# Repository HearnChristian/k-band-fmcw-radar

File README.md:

# K-Band FMCW Radar

A frequency-modulated continuous-wave (FMCW) radar front-end designed in KiCad —
a single-board transceiver intended for **ground-based ranging and weather /
precipitation sensing**. This repository holds the schematic capture, the
project's custom KiCad libraries, and the generated netlist. Work in progress.

## Architecture

FMCW radar works by transmitting a continuous tone whose frequency is swept
(chirped) linearly in time, then mixing the received echo against the
transmitted signal. The frequency of the resulting beat tone is proportional to
target range, so the whole signal chain is built around generating a clean,
linear chirp and digitizing the low-frequency beat note.

```
  Reference        Chirp synth        RF transceiver        Driver amp
  ┌────────┐      ┌──────────┐       ┌──────────────┐      ┌──────────┐
  │  TCXO  │─────▶│ ADF4159  │──────▶│ BGT24LTR11N16│─────▶│AMM-8211PSM│──▶ TX
  │ ref clk│      │ PLL/ramp │       │ 24 GHz Tx/Rx │      │ driver PA │
  └────────┘      └──────────┘       └──────┬───────┘      └──────────┘
                                            │ IF (beat)
                                            ▼
                       ┌──────────┐   ┌──────────┐   ┌──────────┐
                  Rx ──│ OPA1656  │──▶│ ADS8353  │──▶│ FT2232H  │──▶ USB host
                       │ IF amp   │   │ 16b ADC  │   │ USB 2.0  │
                       └──────────┘   └──────────┘   └──────────┘
```

## Key components

| Block | Part | Function |
|-------|------|----------|
| Chirp synthesizer | **ADF4159** | Fractional-N PLL with onboard ramp generator — produces the linear FMCW sweep |
| RF transceiver | **BGT24LTR11N16** | 24 GHz SiGe transmit/receive front-end with integrated VCO and downconversion |
| Driver amplifier | **AMM-8211PSM** | 22–57 GHz GaAs MMIC driver amp boosting the transmit chain |
| IF / baseband | **OPA1656** | Low-noise, low-distortion op-amp conditioning the beat-note signal |
| Data converter | **ADS8353** | Dual 16-bit SAR ADC sampling the IF |
| Host interface | **FT2232HL** | USB 2.0 bridge for control + data streaming |
| Reference clock | **ECS-TXO-2520MV** | TCXO frequency reference |
| Power | **TPS7A4700 / TPS7A2018 / TPS7A2033** | Ultra-low-noise LDOs for clean RF/analog rails |
| Config | **93LC56B** | EEPROM for FT2232 descriptor |

## Custom library work

The **AMM-8211PSM** driver amplifier had no vendor-supplied EDA data — only a
datasheet — so its schematic symbol and PCB footprint were built from scratch
from the Marki Microwave mechanical drawings:

```
AMM-8211PSM.kicad_sym                                          custom symbol
AMM-8211PSM.pretty/QFN-16-1EP_3x3mm_P0.5mm_EP1.1x1.1mm_Marki.kicad_mod   custom footprint
```

The footprint is a 3 × 3 mm 16-lead QFN, 0.5 mm pitch, with a 1.10 × 1.10 mm
exposed ground paddle and a 3 × 3 array of thermal vias, matching the Marki
outline drawing and pin assignment.

## Repository layout

```
Radar1.kicad_pro      KiCad project
Radar1.kicad_sch      Schematic (in progress)
Radar1.kicad_pcb      PCB layout (not yet started)
Radar1.net            Exported netlist
AMM-8211PSM.kicad_sym Custom symbol (see above)
AMM-8211PSM.pretty/   Custom footprint library
sym-lib-table         Project symbol-library table
fp-lib-table          Project footprint-library table
```

## Tools

Designed in [KiCad](https://www.kicad.org/) 9. Open `Radar1.kicad_pro` to view
the schematic.

---

*Author: Christian Hearn*

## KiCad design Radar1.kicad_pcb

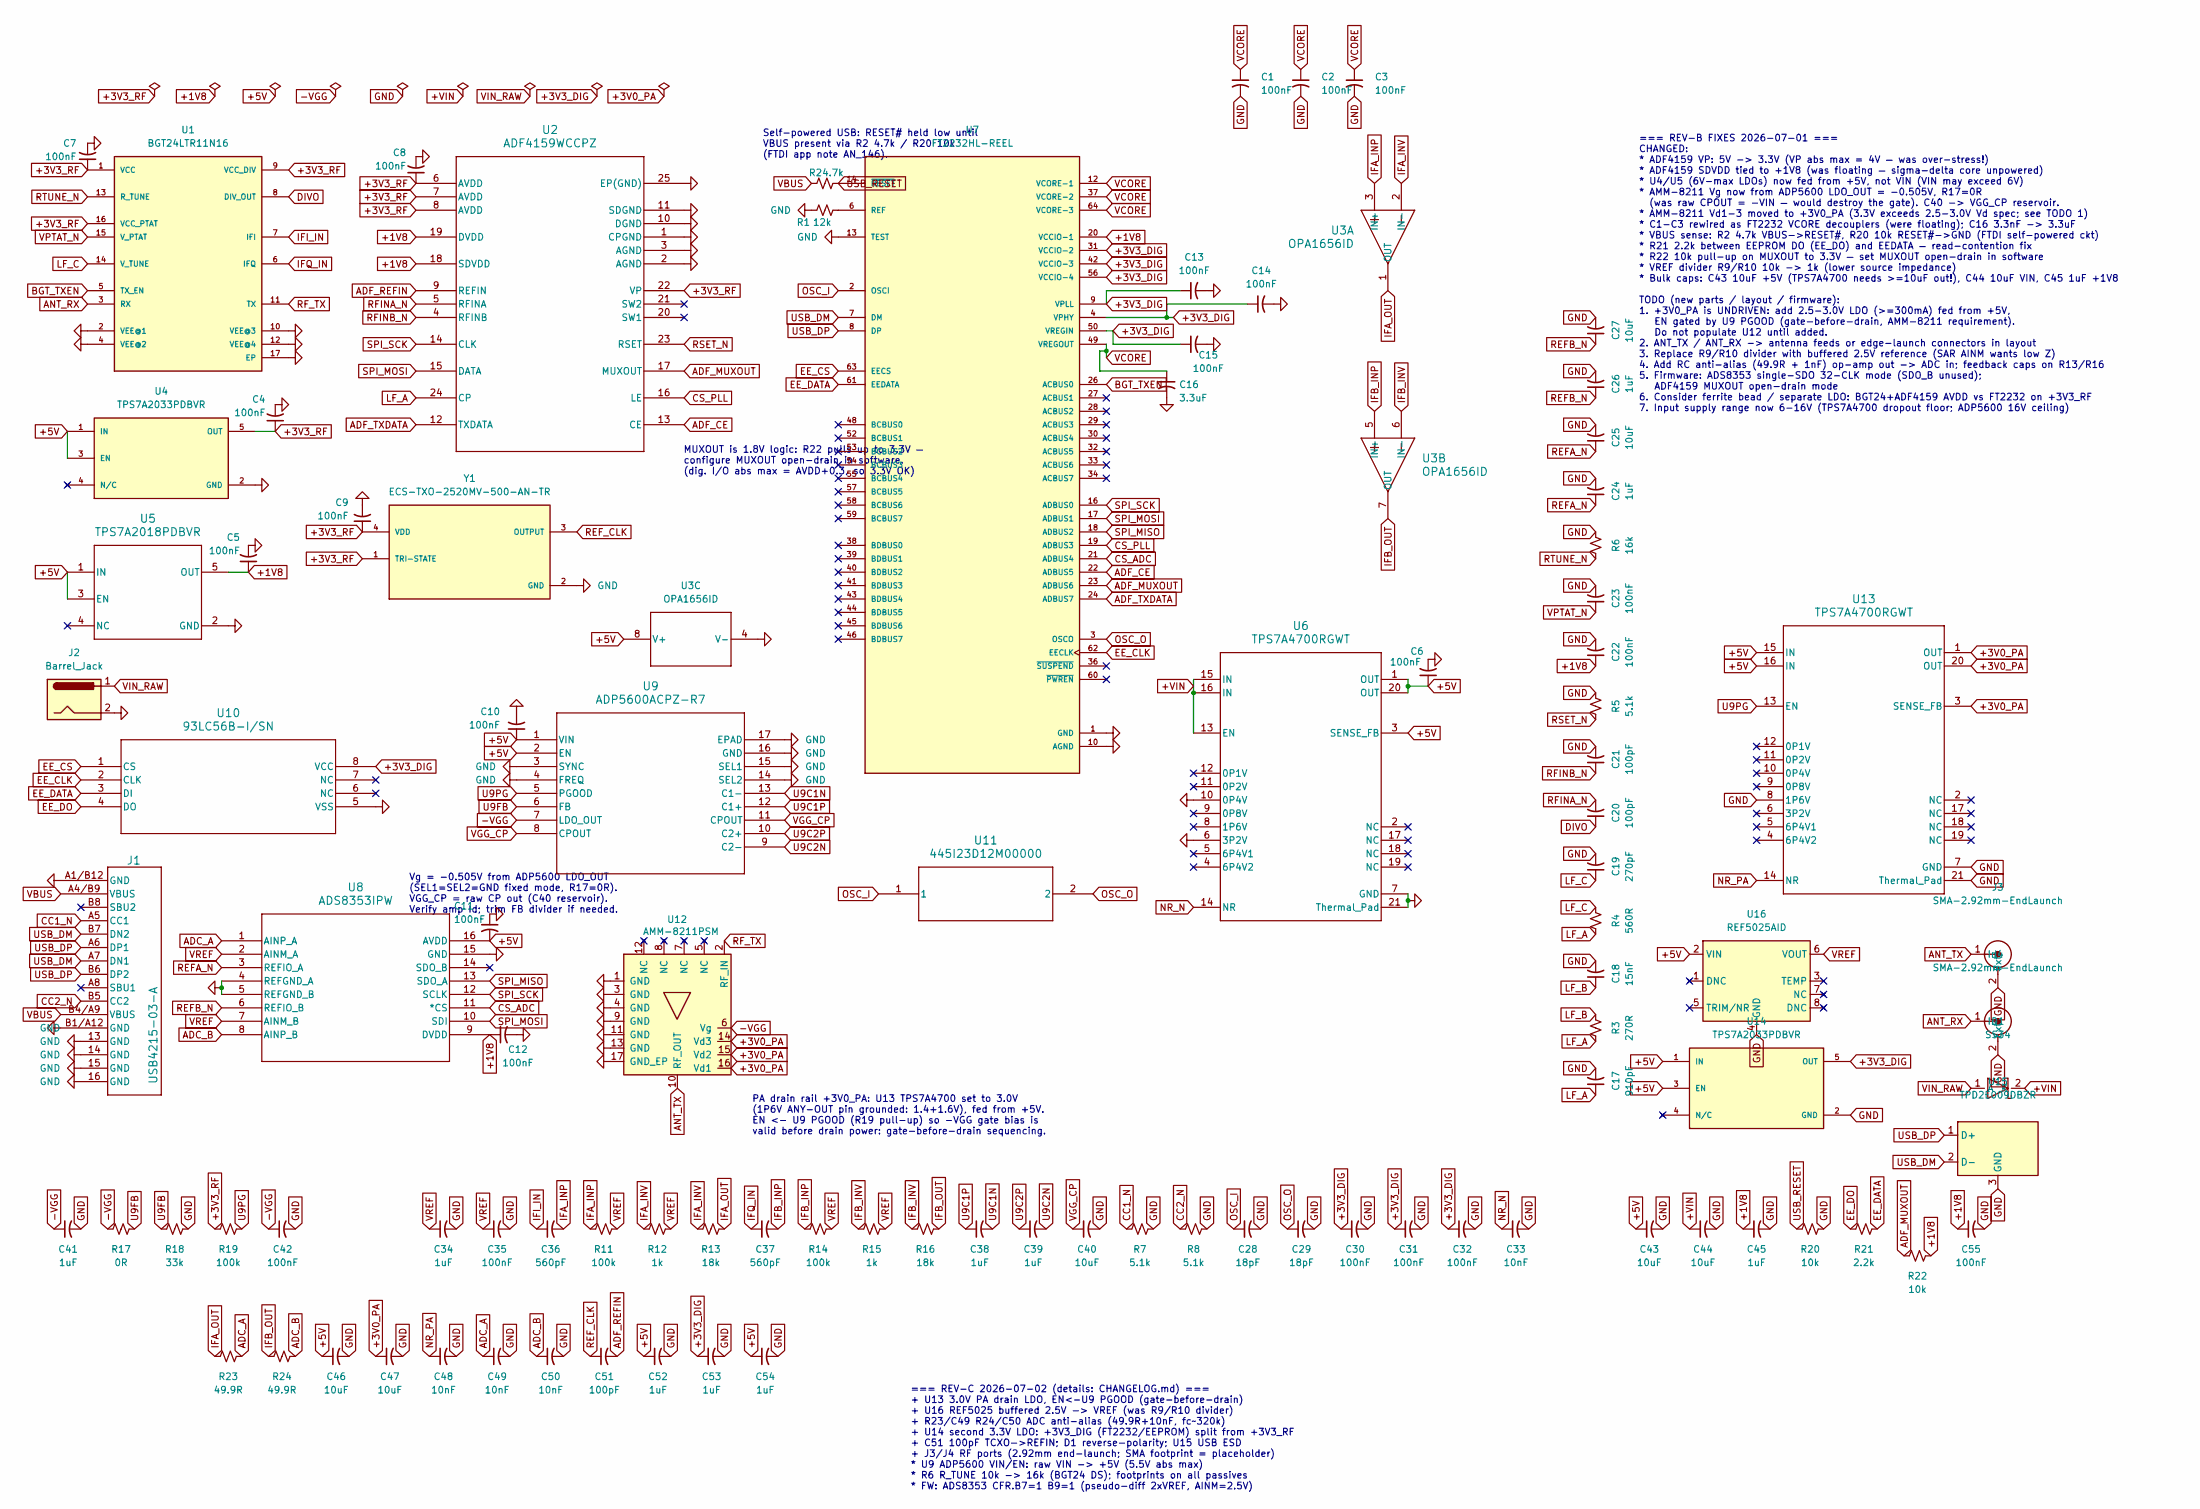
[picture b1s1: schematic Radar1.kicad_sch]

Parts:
C1, C2, C3, C4, C5, C6, C7, C8, C9, C10, C11, C12, C13, C14, C15, C22, C23, C30, C31, C32, C35, C42, C55: 100nF; C_0603_1608Metric
C16: 3.3uF; C_0805_2012Metric
C17: 910pF; C_0603_1608Metric
C18: 15nF; C_0603_1608Metric
C19: 270pF; C_0603_1608Metric
C20, C21, C51: 100pF; C_0603_1608Metric
C24, C26, C34, C38, C39, C41, C45, C52, C53, C54: 1uF; C_0603_1608Metric
C25, C27, C40, C43, C44, C46, C47: 10uF; C_0805_2012Metric
C28, C29: 18pF; C_0603_1608Metric
C33, C48, C49, C50: 10nF; C_0603_1608Metric
C36, C37: 560pF; C_0603_1608Metric
D1: SS34; D_SMA
J1: USB4215-03-A; CONN_8p94X6p5X3p16_12L_GCC
J2: Barrel_Jack; BarrelJack_Horizontal
J3, J4: SMA-2.92mm-EndLaunch; SMA_Amphenol_132289_EdgeMount
R1: 12k; R_0603_1608Metric
R2: 4.7k; R_0603_1608Metric
R3: 270R; R_0603_1608Metric
R4: 560R; R_0603_1608Metric
R5, R7, R8: 5.1k; R_0603_1608Metric
R6: 16k; R_0603_1608Metric
R11, R14, R19: 100k; R_0603_1608Metric
R12, R15: 1k; R_0603_1608Metric
R13, R16: 18k; R_0603_1608Metric
R17: 0R; R_0603_1608Metric
R18: 33k; R_0603_1608Metric
R20, R22: 10k; R_0603_1608Metric
R21: 2.2k; R_0603_1608Metric
R23, R24: 49.9R; R_0603_1608Metric
U1: BGT24LTR11N16; PQFN50P240X240X77-17N-V
U2: ADF4159WCCPZ; CP_24_10
U3: OPA1656ID; D0008A_N
U4, U14: TPS7A2033PDBVR; DBV0005A-IPC_A; PARTREV H
U5: TPS7A2018PDBVR; DBV0005A-IPC_A
U6, U13: TPS7A4700RGWT; RGW0020A-IPC_A
U7: FT2232HL-REEL; QFP50P1200X1200X160-64N
U8: ADS8353IPW; PW16_TEX
U9: ADP5600ACPZ-R7; CP-16-17_ADI
U10: 93LC56B-I/SN; SOIC8-N_MC_MCH
U11: 445I23D12M00000; 445I23D12M00000_CTS
U12: AMM-8211PSM; QFN-16-1EP_3x3mm_P0.5mm_EP1.1x1.1mm_Marki; MPN AMM-8211PSM-22
U15: TPD2E009DBZR; SOT-23
U16: REF5025AID; SOIC-8_3.9x4.9mm_P1.27mm
Y1: ECS-TXO-2520MV-500-AN-TR; OSC_ECS-TXO-2520MV-500-AN-TR; PARTREV 2017

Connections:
+1V8: C5.1, C12.1, C22.1, C45.1, C55.1, R22.2, U2.18 (SDVDD), U2.19 (DVDD), U5.5 (OUT), U7.20 (VCCIO-1), U8.9 (DVDD)
+3V0_PA: C47.1, U12.14 (Vd3), U12.15 (Vd2), U12.16 (Vd1), U13.1 (OUT), U13.3 (SENSE_FB), U13.20 (OUT)
+3V3_DIG: C13.1, C14.1, C15.1, C30.1, C31.1, C32.1, C53.1, U7.4 (VPHY), U7.9 (VPLL), U7.31 (VCCIO-2), U7.42 (VCCIO-3), U7.50 (VREGIN), U7.56 (VCCIO-4), U10.8 (VCC), U14.5 (OUT)
+3V3_RF: C4.1, C7.1, C8.1, C9.1, R19.1, U1.1 (VCC), U1.9 (VCC_DIV), U1.16 (VCC_PTAT), U2.6 (AVDD), U2.7 (AVDD), U2.8 (AVDD), U2.22 (VP), U4.5 (OUT), Y1.1 (TRI-STATE), Y1.4 (VDD)
+5V: C6.1, C10.1, C11.2, C43.1, C46.1, C52.1, C54.1, U3.8 (V+), U4.1 (IN), U4.3 (EN), U5.1 (IN), U5.3 (EN), U6.1 (OUT), U6.3 (SENSE_FB), U6.20 (OUT), U8.16 (AVDD), U9.1 (VIN), U9.2 (EN), U13.15 (IN), U13.16 (IN), U14.1 (IN), U14.3 (EN), U16.2 (VIN)
+VIN: C44.1, D1.2 (K), U6.13 (EN), U6.15 (IN), U6.16 (IN)
-VGG: C41.1, C42.1, R17.1, U9.7 (LDO_OUT), U12.6 (Vg)
ADC_A: C49.1, R23.2, U8.1 (AINP_A)
ADC_B: C50.1, R24.2, U8.8 (AINP_B)
ADF_CE: U2.13 (CE), U7.22 (ADBUS5)
ADF_MUXOUT: R22.1, U2.17 (MUXOUT), U7.23 (ADBUS6)
ADF_REFIN: C51.2, U2.9 (REFIN)
ADF_TXDATA: U2.12 (TXDATA), U7.24 (ADBUS7)
ANT_RX: J4.1 (In), U1.3 (RX)
ANT_TX: J3.1 (In), U12.10 (RF_OUT)
BGT_TXEN: U1.5 (TX_EN), U7.26 (ACBUS0)
CC1_N: J1.A5 (CC1), R7.1
CC2_N: J1.B5 (CC2), R8.1
CS_ADC: U7.21 (ADBUS4), U8.11 (*CS)
CS_PLL: U2.16 (LE), U7.19 (ADBUS3)
DIVO: C20.1, U1.8 (DIV_OUT)
EE_CLK: U7.62 (EECLK), U10.2 (CLK)
EE_CS: U7.63 (EECS), U10.1 (CS)
EE_DATA: R21.2, U7.61 (EEDATA), U10.3 (DI)
EE_DO: R21.1, U10.4 (DO)
GND: C1.2, C2.2, C3.2, C4.2, C5.2, C6.2, C7.2, C8.2, C9.2, C10.2, C11.1, C12.2, C13.2, C14.2, C15.2, C16.2, C17.2, C18.2, C19.2, C21.2, C22.2, C23.2, C24.2, C25.2, C26.2, C27.2, C28.2, C29.2, C30.2, C31.2, C32.2, C33.2, C34.2, C35.2, C40.2, C41.2, C42.2, C43.2, C44.2, C45.2, C46.2, C47.2, C48.2, C49.2, C50.2, C52.2, C53.2, C54.2, C55.2, J1.13 (GND), J1.14 (GND), J1.15 (GND), J1.16 (GND), J1.A1/B12 (GND), J1.B1/A12 (GND), J2.2, J3.2 (Ext), J4.2 (Ext), R1.1, R5.2, R6.2, R7.2, R8.2, R18.2, R20.2, U1.2 (VEE@1), U1.4 (VEE@2), U1.10 (VEE@3), U1.12 (VEE@4), U1.17 (EP), U2.1 (CPGND), U2.2 (AGND), U2.3 (AGND), U2.10 (DGND), U2.11 (SDGND), U2.25 (EP(GND)), U3.4 (V-), U4.2 (GND), U5.2 (GND), U6.6 (3P2V), U6.7 (GND), U6.10 (0P4V), U6.21 (Thermal_Pad), U7.1 (GND), U7.5 (GND), U7.10 (AGND), U7.11 (GND), U7.13 (TEST), U7.15 (GND), U7.25 (GND), U7.35 (GND), U7.47 (GND), U7.51 (GND), U8.4 (REFGND_A), U8.5 (REFGND_B), U8.15 (GND), U9.3 (SYNC), U9.4 (FREQ), U9.14 (SEL2), U9.15 (SEL1), U9.16 (GND), U9.17 (EPAD), U10.5 (VSS), U12.1 (GND), U12.3 (GND), U12.4 (GND), U12.9 (GND), U12.11 (GND), U12.13 (GND), U12.17 (GND_EP), U13.7 (GND), U13.8 (1P6V), U13.21 (Thermal_Pad), U14.2 (GND), U15.3 (GND), U16.4 (GND), Y1.2 (GND)
IFA_INP: C36.2, R11.1, U3.3 (IN+)
IFA_INV: R12.1, R13.1, U3.2 (IN-)
IFA_OUT: R13.2, R23.1, U3.1 (OUT)
IFB_INP: C37.2, R14.1, U3.5 (IN+)
IFB_INV: R15.1, R16.1, U3.6 (IN-)
IFB_OUT: R16.2, R24.1, U3.7 (OUT)
IFI_IN: C36.1, U1.7 (IFI)
IFQ_IN: C37.1, U1.6 (IFQ)
LF_A: C17.1, R3.1, R4.1, U2.24 (CP)
LF_B: C18.1, R3.2
LF_C: C19.1, R4.2, U1.14 (V_TUNE)
NR_N: C33.1, U6.14 (NR)
NR_PA: C48.1, U13.14 (NR)
unnamed: R1.2, U7.6 (REF)
OSC_I: C28.1, U7.2 (OSCI), U11.1
OSC_O: C29.1, U7.3 (OSCO), U11.2
REFA_N: C24.1, C25.1, U8.3 (REFIO_A)
REFB_N: C26.1, C27.1, U8.6 (REFIO_B)
REF_CLK: C51.1, Y1.3 (OUTPUT)
RFINA_N: C20.2, U2.5 (RFINA)
RFINB_N: C21.1, U2.4 (RFINB)
RF_TX: U1.11 (TX), U12.2 (RF_IN)
RSET_N: R5.1, U2.23 (RSET)
RTUNE_N: R6.1, U1.13 (R_TUNE)
SPI_MISO: U7.18 (ADBUS2), U8.13 (SDO_A)
SPI_MOSI: U2.15 (DATA), U7.17 (ADBUS1), U8.10 (SDI)
SPI_SCK: U2.14 (CLK), U7.16 (ADBUS0), U8.12 (SCLK)
U9C1N: C38.2, U9.13 (C1-)
U9C1P: C38.1, U9.12 (C1+)
U9C2N: C39.2, U9.9 (C2-)
U9C2P: C39.1, U9.10 (C2+)
U9FB: R17.2, R18.1, U9.6 (FB)
U9PG: R19.2, U9.5 (PGOOD), U13.13 (EN)
USB_DM: J1.A7 (DN1), J1.B7 (DN2), U7.7 (DM), U15.2 (D-)
USB_DP: J1.A6 (DP1), J1.B6 (DP2), U7.8 (DP), U15.1 (D+)
USB_RESET: R2.2, R20.1, U7.14 (~RESET)
VBUS: J1.A4/B9 (VBUS), J1.B4/A9 (VBUS), R2.1
VCORE: C1.1, C2.1, C3.1, C16.1, U7.12 (VCORE-1), U7.37 (VCORE-2), U7.49 (VREGOUT), U7.64 (VCORE-3)
VGG_CP: C40.1, U9.8 (CPOUT), U9.11 (CPOUT)
VIN_RAW: D1.1 (A), J2.1
VPTAT_N: C23.1, U1.15 (V_PTAT)
VREF: C34.1, C35.1, R11.2, R12.2, R14.2, R15.2, U8.2 (AINM_A), U8.7 (AINM_B), U16.6 (VOUT)

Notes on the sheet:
Vg = -0.505V from ADP5600 LDO_OUT (SEL1=SEL2=GND fixed mode, R17=0R). VGG_CP = raw CP out (C40 reservoir). Verify amp Id; trim FB divider if needed.
=== REV-C 2026-07-02 (details: CHANGELOG.md) === + U13 3.0V PA drain LDO, EN<-U9 PGOOD (gate-before-drain) + U16 REF5025 buffered 2.5V -> VREF (was R9/R10 divider) + R23/C49 R24/C50 ADC anti-alias (49.9R+10nF, fc~320k) + U14 second 3.3V LDO: +3V3_DIG (FT2232/EEPROM) split from +3V3_RF + C51 100pF T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
Self-powered USB: RESET# held low until VBUS present via R2 4.7k / R20 10k (FTDI app note AN_146).
=== REV-B FIXES 2026-07-01 === CHANGED: * ADF4159 VP: 5V -> 3.3V (VP abs max = 4V — was over-stress!) * ADF4159 SDVDD tied to +1V8 (was floating — sigma-delta core unpowered) * U4/U5 (6V-max LDOs) now fed from +5V, not VIN (VIN may exceed 6V) * AMM-8211 Vg now from ADP5600 LDO_OUT = -0.505V, R17=0R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
MUXOUT is 1.8V logic: R22 pulls up to 3.3V — configure MUXOUT open-drain in software. (dig. I/O abs max = AVDD+0.3, so 3.3V OK)
PA drain rail +3V0_PA: U13 TPS7A4700 set to 3.0V (1P6V ANY-OUT pin grounded: 1.4+1.6V), fed from +5V. EN <- U9 PGOOD (R19 pull-up) so -VGG gate bias is valid before drain power: gate-before-drain sequencing.

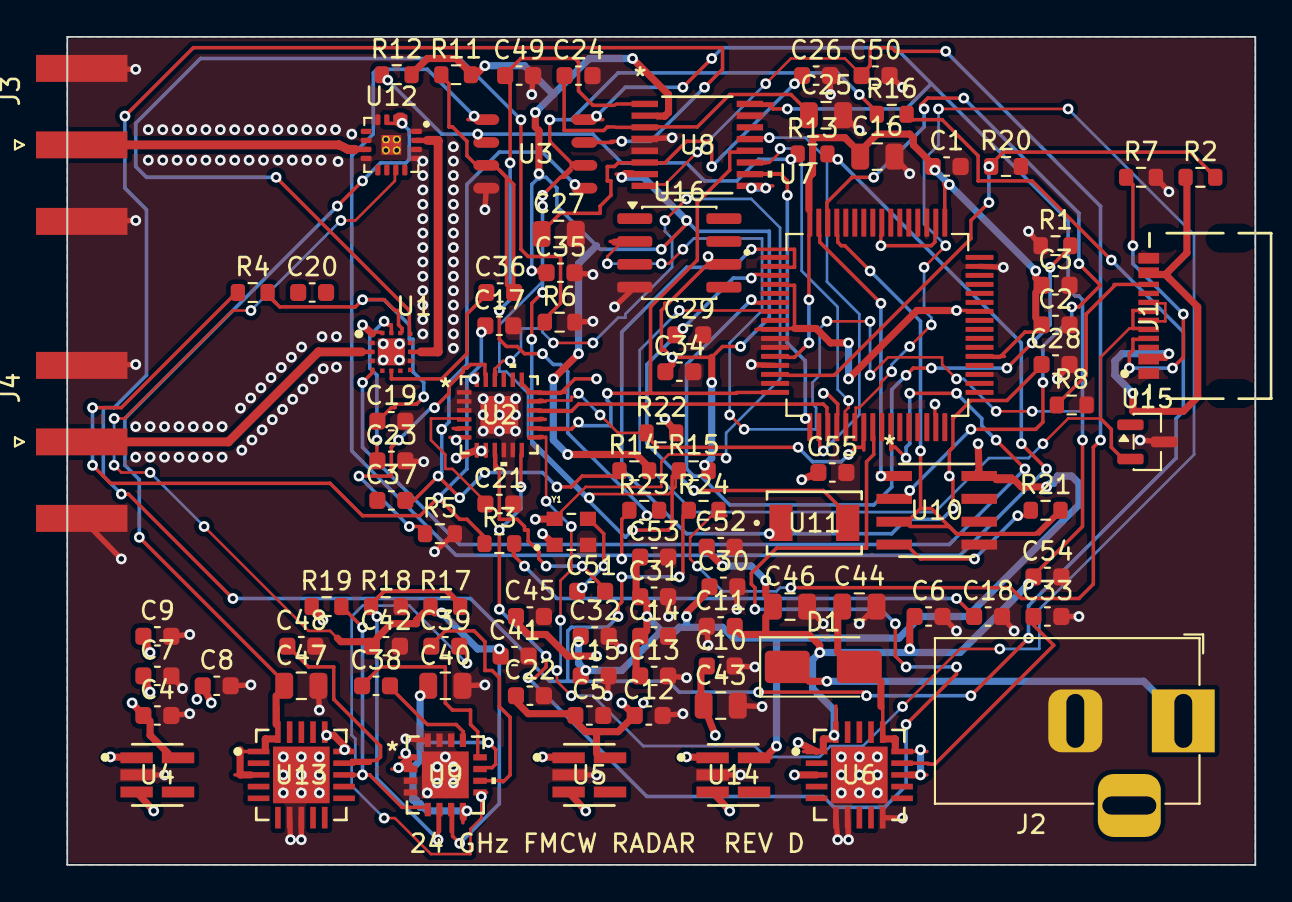
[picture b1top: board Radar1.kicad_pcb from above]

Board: 4 copper layers, 66.0 x 46.0 mm, 99 parts (0 on the bottom side), 68 nets.
